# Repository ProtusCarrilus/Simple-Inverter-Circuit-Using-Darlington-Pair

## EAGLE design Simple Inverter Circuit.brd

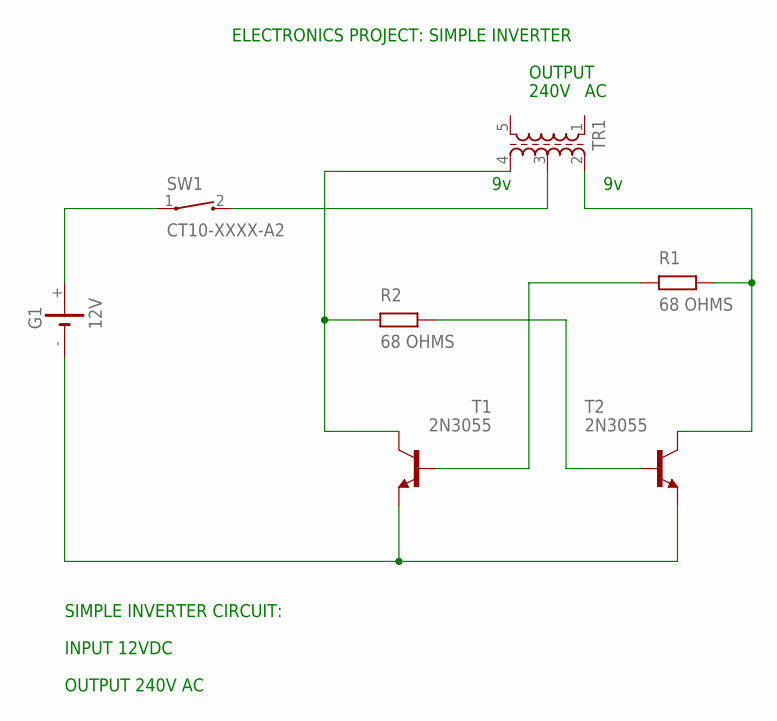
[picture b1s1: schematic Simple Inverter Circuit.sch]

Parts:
G1: 12V; CH291-1220LF
SW1: CT10-XXXX-A2
T1, T2: 2N3055; TO3
TR1: SM-T4-2T; SM-T4

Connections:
unnamed: G1.+, SW1.1
unnamed: G1.-, T1.E, T2.E
unnamed: T2.C, T2.C/ (C), TR1.2
unnamed: SW1.2, TR1.3
unnamed: T1.C, T1.C/ (C), TR1.4

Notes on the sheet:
240V
SIMPLE INVERTER CIRCUIT:
INPUT 12VDC
OUTPUT 240V AC
OUTPUT
ELECTRONICS PROJECT: SIMPLE INVERTER

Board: 2 copper layers, 5 parts (0 on the bottom side), 5 nets, no tracks yet.
